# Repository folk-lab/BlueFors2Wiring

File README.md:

# BlueFors2Wiring
Eagle source files for all PCB used in the wiring of BlueFors2

A comprehensive breakdown of how all these parts fit into the fridge can be found on the [Folk Lab wiki](https://qdot-server.phas.ubc.ca/wiki/machines:bluefors_fridge_2:wiring)

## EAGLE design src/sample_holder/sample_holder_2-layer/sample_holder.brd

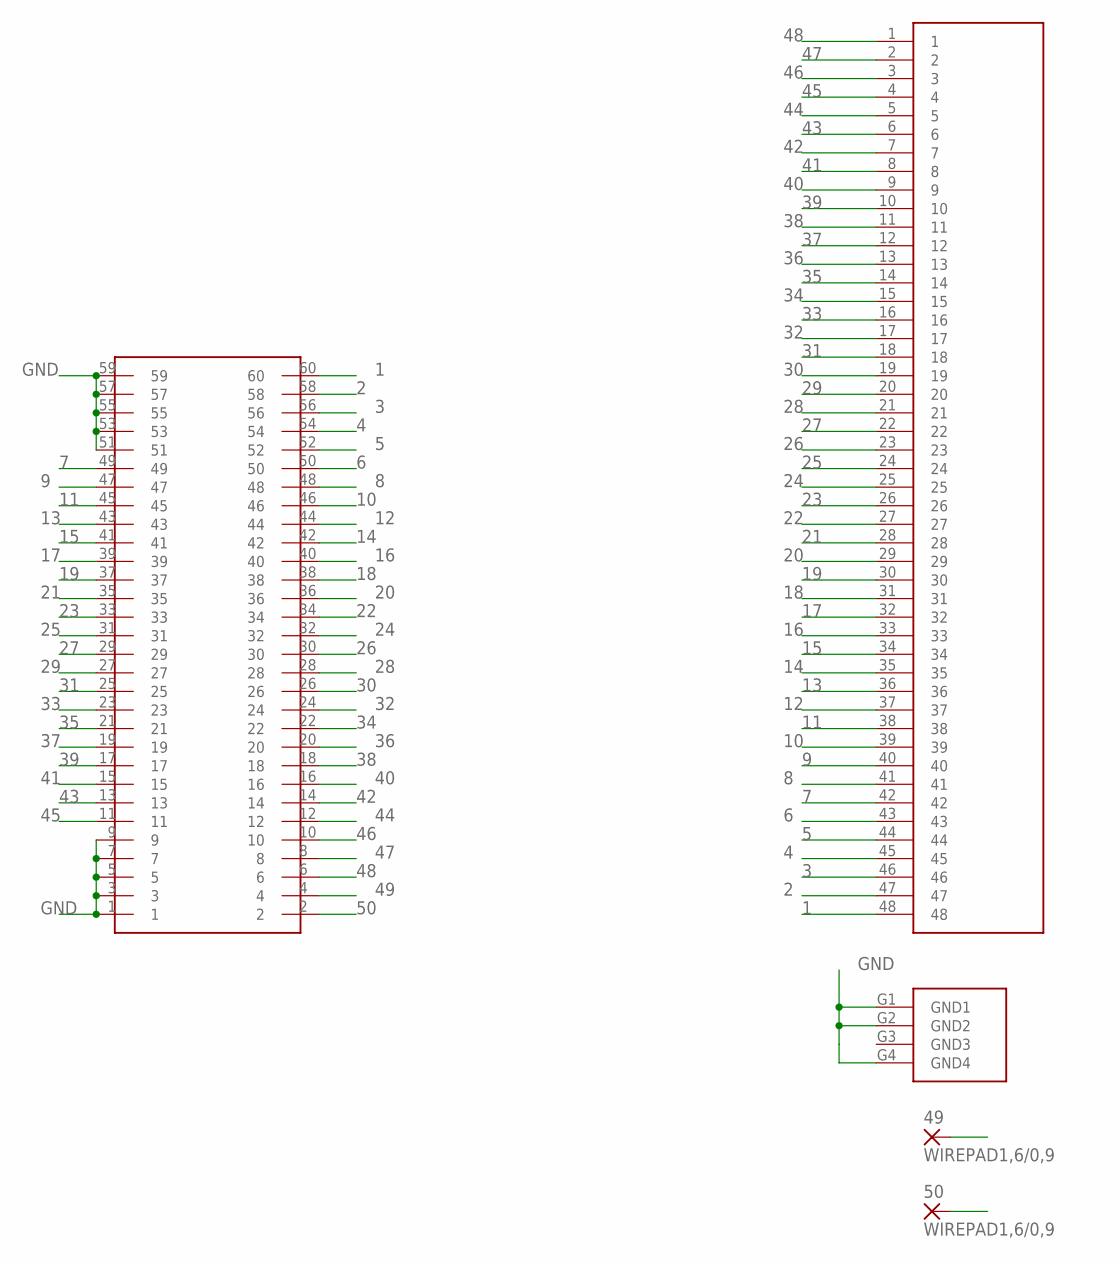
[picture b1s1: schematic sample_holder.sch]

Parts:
49, 50: WIREPAD1,6/0,9; 1,6/0,9
U$1: MEC5-030-CARD-ALL; MEC-030-CARD-ALL
U$2: FOLKLAB-48PADS

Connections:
1: U$1.60, U$2.48
2: U$1.58, U$2.47
3: U$1.56, U$2.46
4: U$1.54, U$2.45
5: U$1.52, U$2.44
6: U$1.50, U$2.43
7: U$1.49, U$2.42
8: U$1.48, U$2.41
9: U$1.47, U$2.40
10: U$1.46, U$2.39
11: U$1.45, U$2.38
12: U$1.44, U$2.37
13: U$1.43, U$2.36
14: U$1.42, U$2.35
15: U$1.41, U$2.34
16: U$1.40, U$2.33
17: U$1.39, U$2.32
18: U$1.38, U$2.31
19: U$1.37, U$2.30
20: U$1.36, U$2.29
21: U$1.35, U$2.28
22: U$1.34, U$2.27
23: U$1.33, U$2.26
24: U$1.32, U$2.25
25: U$1.31, U$2.24
26: U$1.30, U$2.23
27: U$1.29, U$2.22
28: U$1.28, U$2.21
29: U$1.27, U$2.20
30: U$1.26, U$2.19
31: U$1.25, U$2.18
32: U$1.24, U$2.17
33: U$1.23, U$2.16
34: U$1.22, U$2.15
35: U$1.21, U$2.14
36: U$1.20, U$2.13
37: U$1.19, U$2.12
38: U$1.18, U$2.11
39: U$1.17, U$2.10
40: U$1.16, U$2.9
41: U$1.15, U$2.8
42: U$1.14, U$2.7
43: U$1.13, U$2.6
44: U$1.12, U$2.5
45: U$1.11, U$2.4
46: U$1.10, U$2.3
47: U$1.8, U$2.2
48: U$1.6, U$2.1
49: 49.1, U$1.4
50: 50.1, U$1.2
GND: U$1.1, U$1.3, U$1.5, U$1.7, U$1.9, U$1.51, U$1.53, U$1.55, U$1.57, U$1.59, U$2.G1 (GND1), U$2.G2 (GND2), U$2.G4 (GND4)

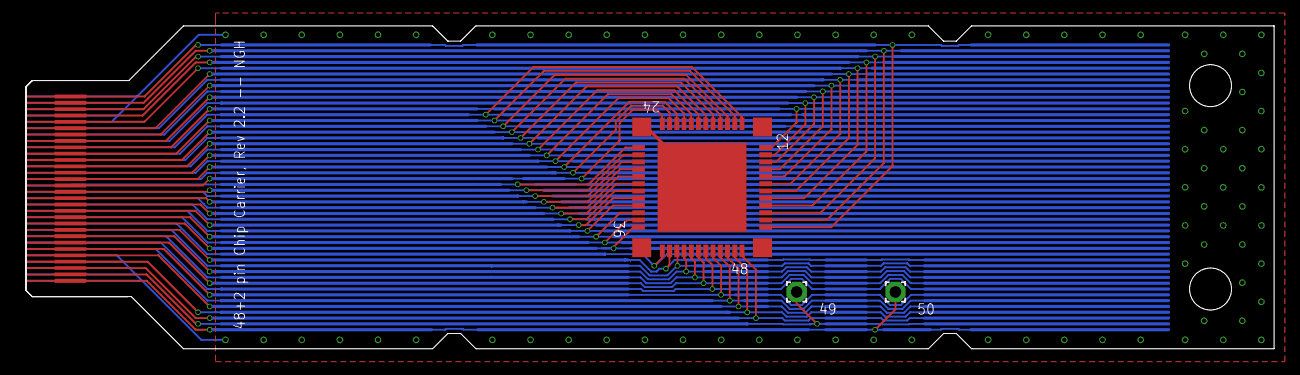
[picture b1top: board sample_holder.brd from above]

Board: 2 copper layers, 98.2 x 25.4 mm, 4 parts (0 on the bottom side), 51 nets.

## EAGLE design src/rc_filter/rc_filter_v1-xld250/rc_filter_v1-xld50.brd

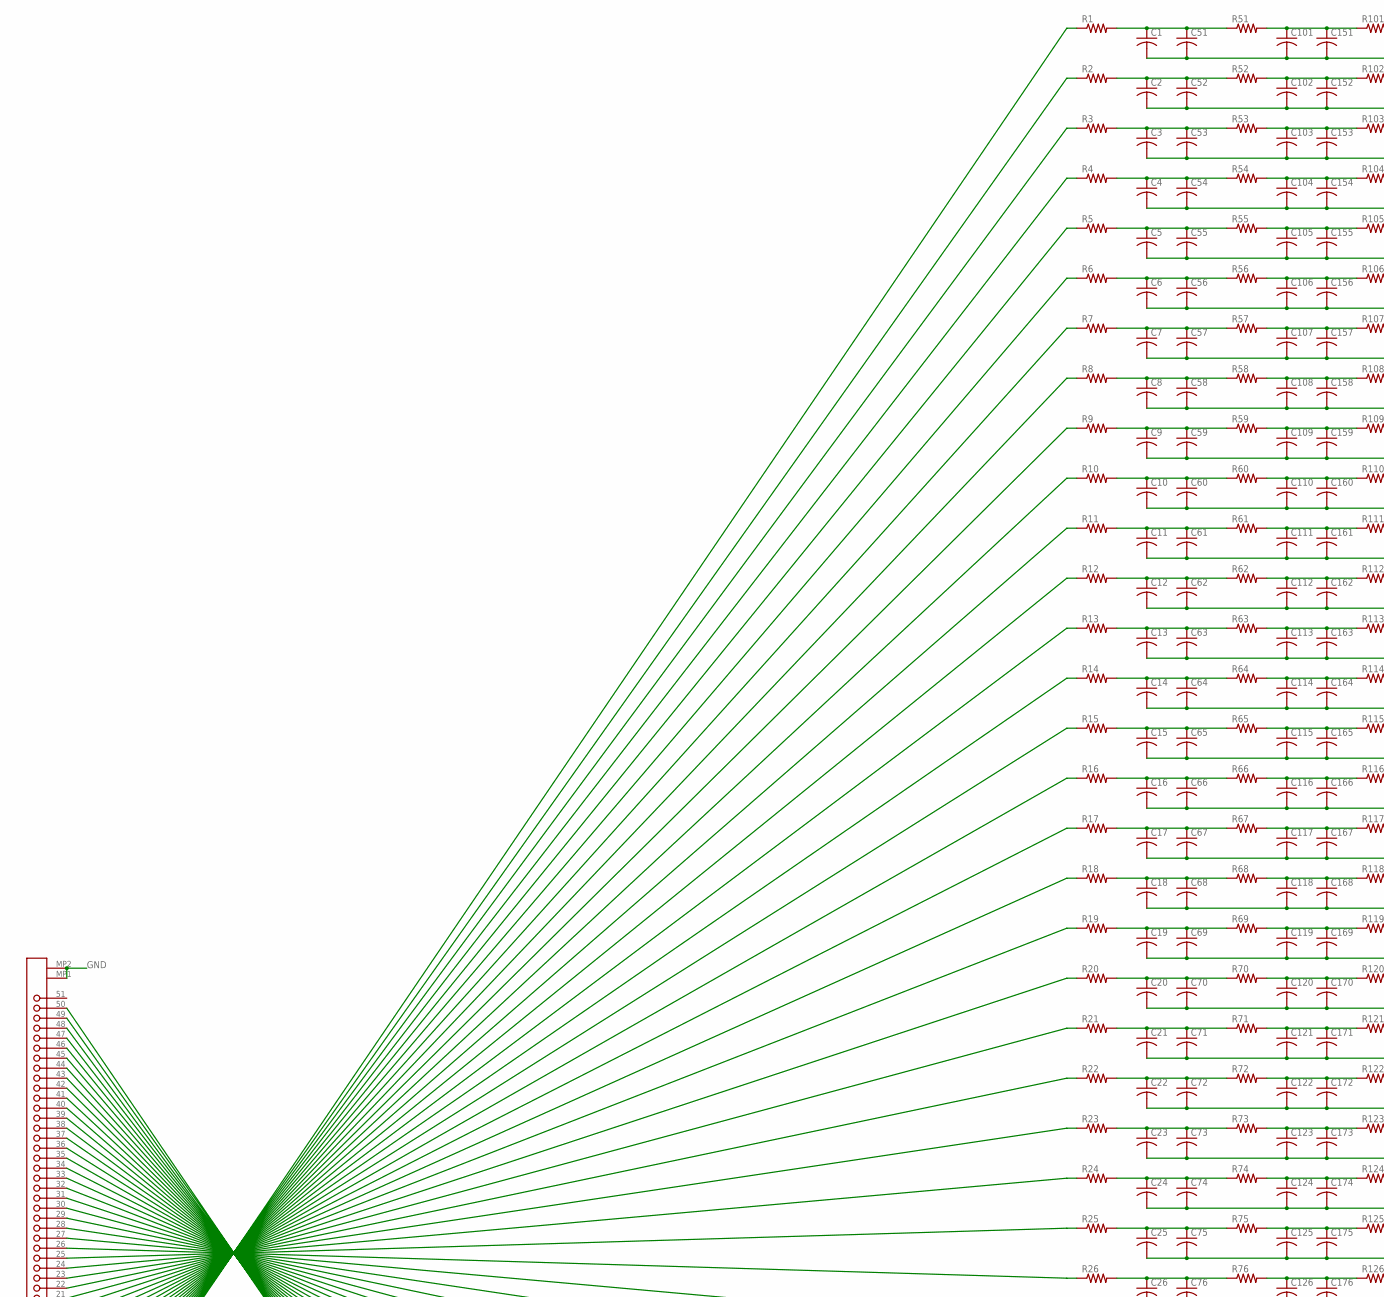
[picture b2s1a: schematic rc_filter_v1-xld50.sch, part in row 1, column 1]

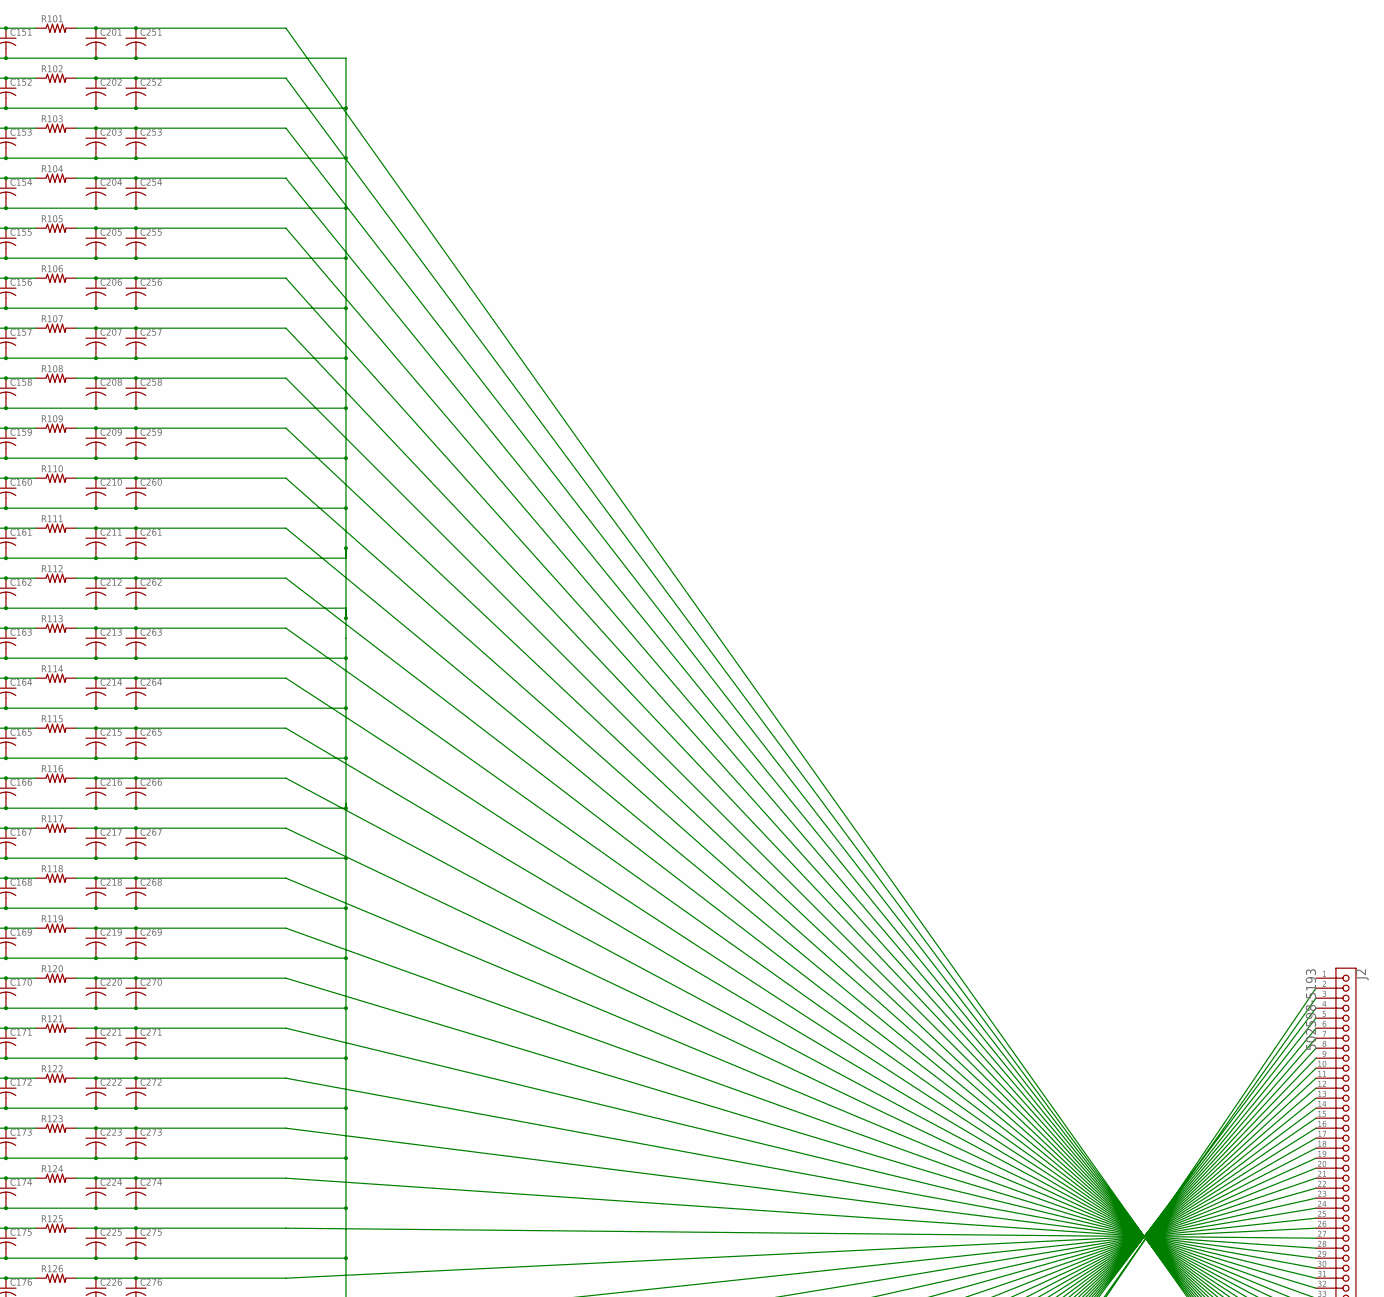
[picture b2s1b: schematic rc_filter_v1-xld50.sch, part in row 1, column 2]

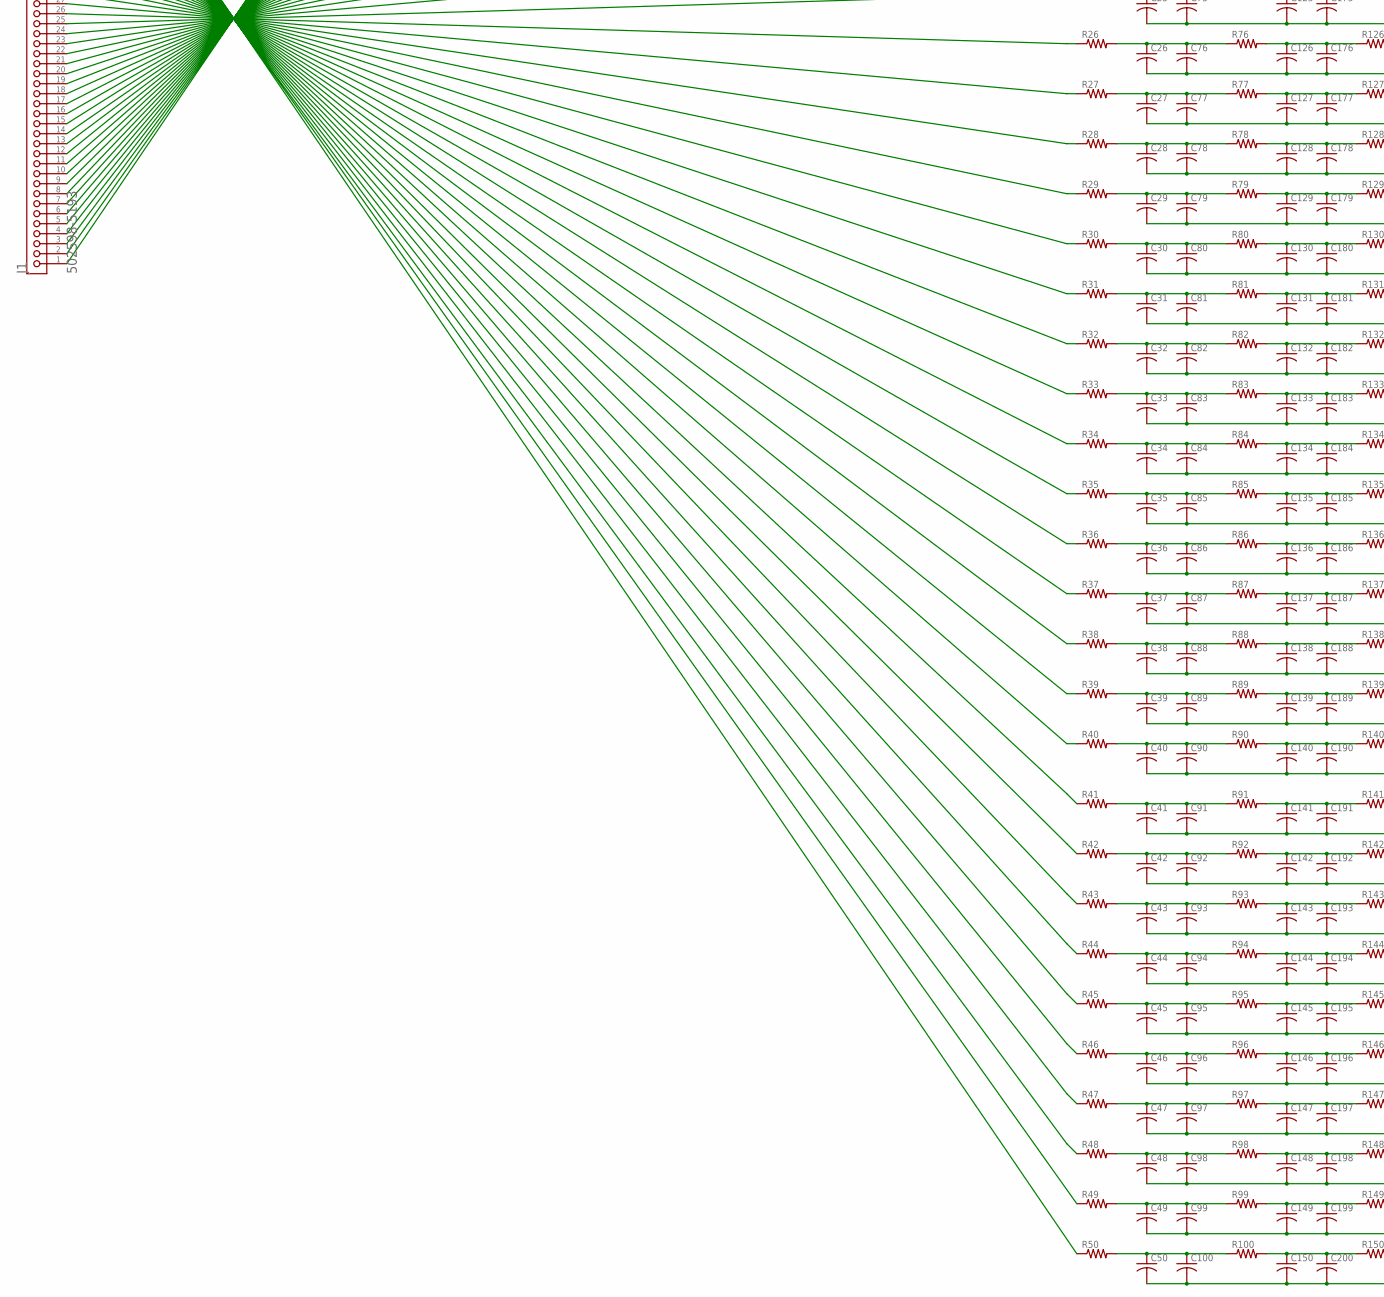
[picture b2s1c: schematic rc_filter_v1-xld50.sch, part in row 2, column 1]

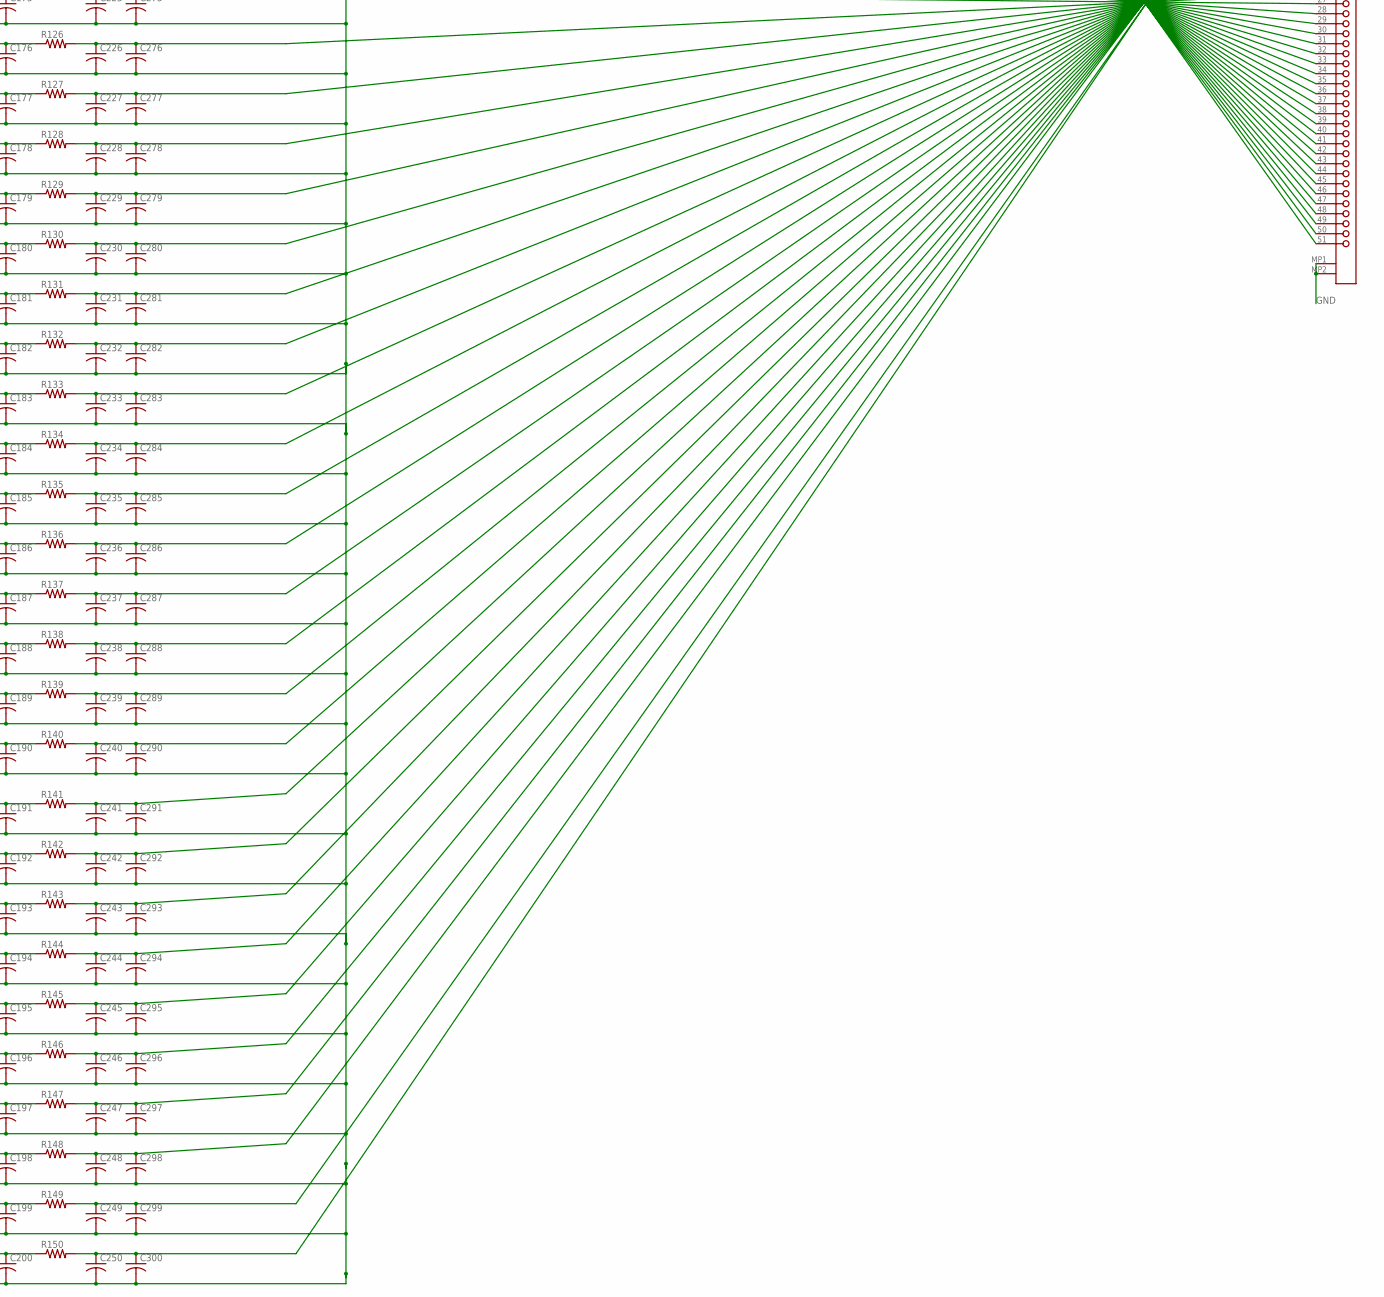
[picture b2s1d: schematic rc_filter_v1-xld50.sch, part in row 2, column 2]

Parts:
C1, C2, C3, C4, C5, C6, C7, C8, C9, C10, C11, C12, C13, C14, C15, C16, C17, C18, C19, C20, C21, C22, C23, C24, C25, C26, C27, C28, C29, C30, C31, C32, C33, C34, C35, C36, C37, C38, C39, C40, C41, C42, C43, C44, C45, C46, C47, C48, C49, C50, C51, C52, C53, C54, C55, C56, C57, C58, C59, C60, C61, C62, C63, C64, C65, C66, C67, C68, C69, C70, C71, C72, C73, C74, C75, C76, C77, C78, C79, C80, C81, C82, C83, C84, C85, C86, C87, C88, C89, C90, C91, C92, C93, C94, C95, C96, C97, C98, C99, C100, C101, C102, C103, C104, C105, C106, C107, C108, C109, C110, C111, C112, C113, C114, C115, C116, C117, C118, C119, C120, C121, C122, C123, C124, C125, C126, C127, C128, C129, C130, C131, C132, C133, C134, C135, C136, C137, C138, C139, C140, C141, C142, C143, C144, C145, C146, C147, C148, C149, C150, C151, C152, C153, C154, C155, C156, C157, C158, C159, C160, C161, C162, C163, C164, C165, C166, C167, C168, C169, C170, C171, C172, C173, C174, C175, C176, C177, C178, C179, C180, C181, C182, C183, C184, C185, C186, C187, C188, C189, C190, C191, C192, C193, C194, C195, C196, C197, C198, C199, C200, C201, C202, C203, C204, C205, C206, C207, C208, C209, C210, C211, C212, C213, C214, C215, C216, C217, C218, C219, C220, C221, C222, C223, C224, C225, C226, C227, C228, C229, C230, C231, C232, C233, C234, C235, C236, C237, C238, C239, C240, C241, C242, C243, C244, C245, C246, C247, C248, C249, C250, C251, C252, C253, C254, C255, C256, C257, C258, C259, C260, C261, C262, C263, C264, C265, C266, C267, C268, C269, C270, C271, C272, C273, C274, C275, C276, C277, C278, C279, C280, C281, C282, C283, C284, C285, C286, C287, C288, C289, C290, C291, C292, C293, C294, C295, C296, C297, C298, C299, C300: C-USC0402; C0402
J1, J2: MOLEX_502598-5193MOLEX_502598-5193_0_0; MOLEX_502598-5193_0
R1, R2, R3, R4, R5, R6, R7, R8, R9, R10, R11, R12, R13, R14, R15, R16, R17, R18, R19, R20, R21, R22, R23, R24, R25, R26, R27, R28, R29, R30, R31, R32, R33, R34, R35, R36, R37, R38, R39, R40, R41, R42, R43, R44, R45, R46, R47, R48, R49, R50, R51, R52, R53, R54, R55, R56, R57, R58, R59, R60, R61, R62, R63, R64, R65, R66, R67, R68, R69, R70, R71, R72, R73, R74, R75, R76, R77, R78, R79, R80, R81, R82, R83, R84, R85, R86, R87, R88, R89, R90, R91, R92, R93, R94, R95, R96, R97, R98, R99, R100, R101, R102, R103, R104, R105, R106, R107, R108, R109, R110, R111, R112, R113, R114, R115, R116, R117, R118, R119, R120, R121, R122, R123, R124, R125, R126, R127, R128, R129, R130, R131, R132, R133, R134, R135, R136, R137, R138, R139, R140, R141, R142, R143, R144, R145, R146, R147, R148, R149, R150: R-US_R0402; R0402

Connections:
F1: J1.1, R1.1
F2: J1.2, R2.1
F3: J1.3, R3.1
F4: J1.4, R4.1
F5: J1.5, R5.1
F6: J1.6, R6.1
F7: J1.7, R7.1
F8: J1.8, R8.1
F9: J1.9, R9.1
F10: J1.10, R10.1
F11: J1.11, R11.1
F12: J1.12, R12.1
F13: J1.13, R13.1
F14: J1.14, R14.1
F15: J1.15, R15.1
F16: J1.16, R16.1
F17: J1.17, R17.1
F18: J1.18, R18.1
F19: J1.19, R19.1
F20: J1.20, R20.1
F21: J1.21, R21.1
F22: J1.22, R22.1
F23: J1.23, R23.1
F24: J1.24, R24.1
F25: J1.25, R25.1
F26: J1.26, R26.1
F27: J1.27, R27.1
F28: J1.28, R28.1
F29: J1.29, R29.1
F30: J1.30, R30.1
F31: J1.31, R31.1
F32: J1.32, R32.1
F33: J1.33, R33.1
F34: J1.34, R34.1
F35: J1.35, R35.1
F36: J1.36, R36.1
F37: J1.37, R37.1
F38: J1.38, R38.1
F39: J1.39, R39.1
F40: J1.40, R40.1
F41: J1.41, R41.1
F42: J1.42, R42.1
F43: J1.43, R43.1
F44: J1.44, R44.1
F45: J1.45, R45.1
F46: J1.46, R46.1
F47: J1.47, R47.1
F48: J1.48, R48.1
F49: J1.49, R49.1
F50: J1.50, R50.1
G1: C201.1, C251.1, J2.51, R101.2
G2: C202.1, C252.1, J2.50, R102.2
G3: C203.1, C253.1, J2.49, R103.2
G4: C204.1, C254.1, J2.48, R104.2
G5: C205.1, C255.1, J2.47, R105.2
G6: C206.1, C256.1, J2.46, R106.2
G7: C207.1, C257.1, J2.45, R107.2
G8: C208.1, C258.1, J2.44, R108.2
G9: C209.1, C259.1, J2.43, R109.2
G10: C210.1, C260.1, J2.42, R110.2
G11: C211.1, C261.1, J2.41, R111.2
G12: C212.1, C262.1, J2.40, R112.2
G13: C213.1, C263.1, J2.39, R113.2
G14: C214.1, C264.1, J2.38, R114.2
G15: C215.1, C265.1, J2.37, R115.2
G16: C216.1, C266.1, J2.36, R116.2
G17: C217.1, C267.1, J2.35, R117.2
G18: C218.1, C268.1, J2.34, R118.2
G19: C219.1, C269.1, J2.33, R119.2
G20: C220.1, C270.1, J2.32, R120.2
G21: C221.1, C271.1, J2.31, R121.2
G22: C222.1, C272.1, J2.30, R122.2
G23: C223.1, C273.1, J2.29, R123.2
G24: C224.1, C274.1, J2.28, R124.2
G25: C225.1, C275.1, J2.27, R125.2
G26: C226.1, C276.1, J2.26, R126.2
G27: C227.1, C277.1, J2.25, R127.2
G28: C228.1, C278.1, J2.24, R128.2
G29: C229.1, C279.1, J2.23, R129.2
G30: C230.1, C280.1, J2.22, R130.2
G31: C231.1, C281.1, J2.21, R131.2
G32: C232.1, C282.1, J2.20, R132.2
G33: C233.1, C283.1, J2.19, R133.2
G34: C234.1, C284.1, J2.18, R134.2
G35: C235.1, C285.1, J2.17, R135.2
G36: C236.1, C286.1, J2.16, R136.2
G37: C237.1, C287.1, J2.15, R137.2
G38: C238.1, C288.1, J2.14, R138.2
G39: C239.1, C289.1, J2.13, R139.2
G40: C240.1, C290.1, J2.12, R140.2
G41: C241.1, C291.1, J2.11, R141.2
G42: C242.1, C292.1, J2.10, R142.2
G43: C243.1, C293.1, J2.9, R143.2
G44: C244.1, C294.1, J2.8, R144.2
G45: C245.1, C295.1, J2.7, R145.2
G46: C246.1, C296.1, J2.6, R146.2
G47: C247.1, C297.1, J2.5, R147.2
G48: C248.1, C298.1, J2.4, R148.2
G49: C249.1, C299.1, J2.3, R149.2
G50: C250.1, C300.1, J2.2, R150.2
GND: C1.2, C2.2, C3.2, C4.2, C5.2, C6.2, C7.2, C8.2, C9.2, C10.2, C11.2, C12.2, C13.2, C14.2, C15.2, C16.2, C17.2, C18.2, C19.2, C20.2, C21.2, C22.2, C23.2, C24.2, C25.2, C26.2, C27.2, C28.2, C29.2, C30.2, C31.2, C32.2, C33.2, C34.2, C35.2, C36.2, C37.2, C38.2, C39.2, C40.2, C41.2, C42.2, C43.2, C44.2, C45.2, C46.2, C47.2, C48.2, C49.2, C50.2, C51.2, C52.2, C53.2, C54.2, C55.2, C56.2, C57.2, C58.2, C59.2, C60.2, C61.2, C62.2, C63.2, C64.2, C65.2, C66.2, C67.2, C68.2, C69.2, C70.2, C71.2, C72.2, C73.2, C74.2, C75.2, C76.2, C77.2, C78.2, C79.2, C80.2, C81.2, C82.2, C83.2, C84.2, C85.2, C86.2, C87.2, C88.2, C89.2, C90.2, C91.2, C92.2, C93.2, C94.2, C95.2, C96.2, C97.2, C98.2, C99.2, C100.2, C101.2, C102.2, C103.2, C104.2, C105.2, C106.2, C107.2, C108.2, C109.2, C110.2, C111.2, C112.2, C113.2, C114.2, C115.2, C116.2, C117.2, C118.2, C119.2, C120.2, C121.2, C122.2, C123.2, C124.2, C125.2, C126.2, C127.2, C128.2, C129.2, C130.2, C131.2, C132.2, C133.2, C134.2, C135.2, C136.2, C137.2, C138.2, C139.2, C140.2, C141.2, C142.2, C143.2, C144.2, C145.2, C146.2, C147.2, C148.2, C149.2, C150.2, C151.2, C152.2, C153.2, C154.2, C155.2, C156.2, C157.2, C158.2, C159.2, C160.2, C161.2, C162.2, C163.2, C164.2, C165.2, C166.2, C167.2, C168.2, C169.2, C170.2, C171.2, C172.2, C173.2, C174.2, C175.2, C176.2, C177.2, C178.2, C179.2, C180.2, C181.2, C182.2, C183.2, C184.2, C185.2, C186.2, C187.2, C188.2, C189.2, C190.2, C191.2, C192.2, C193.2, C194.2, C195.2, C196.2, C197.2, C198.2, C199.2, C200.2, C201.2, C202.2, C203.2, C204.2, C205.2, C206.2, C207.2, C208.2, C209.2, C210.2, C211.2, C212.2, C213.2, C214.2, C215.2, C216.2, C217.2, C218.2, C219.2, C220.2, C221.2, C222.2, C223.2, C224.2, C225.2, C226.2, C227.2, C228.2, C229.2, C230.2, C231.2, C232.2, C233.2, C234.2, C235.2, C236.2, C237.2, C238.2, C239.2, C240.2, C241.2, C242.2, C243.2, C244.2, C245.2, C246.2, C247.2, C248.2, C249.2, C250.2, C251.2, C252.2, C253.2, C254.2, C255.2, C256.2, C257.2, C258.2, C259.2, C260.2, C261.2, C262.2, C263.2, C264.2, C265.2, C266.2, C267.2, C268.2, C269.2, C270.2, C271.2, C272.2, C273.2, C274.2, C275.2, C276.2, C277.2, C278.2, C279.2, C280.2, C281.2, C282.2, C283.2, C284.2, C285.2, C286.2, C287.2, C288.2, C289.2, C290.2, C291.2, C292.2, C293.2, C294.2, C295.2, C296.2, C297.2, C298.2, C299.2, C300.2, J1.MP1, J1.MP2, J2.MP1, J2.MP2
unnamed: C4.1, C54.1, R4.2, R54.1
unnamed: C104.1, C154.1, R54.2, R104.1
unnamed: C3.1, C53.1, R3.2, R53.1
unnamed: C103.1, C153.1, R53.2, R103.1
unnamed: C6.1, C56.1, R6.2, R56.1
unnamed: C106.1, C156.1, R56.2, R106.1
unnamed: C5.1, C55.1, R5.2, R55.1
unnamed: C105.1, C155.1, R55.2, R105.1
unnamed: C8.1, C58.1, R8.2, R58.1
unnamed: C108.1, C158.1, R58.2, R108.1
unnamed: C7.1, C57.1, R7.2, R57.1
unnamed: C107.1, C157.1, R57.2, R107.1
unnamed: C10.1, C60.1, R10.2, R60.1
unnamed: C110.1, C160.1, R60.2, R110.1
unnamed: C9.1, C59.1, R9.2, R59.1
unnamed: C109.1, C159.1, R59.2, R109.1
unnamed: C2.1, C52.1, R2.2, R52.1
unnamed: C102.1, C152.1, R52.2, R102.1
unnamed: C1.1, C51.1, R1.2, R51.1
unnamed: C101.1, C151.1, R51.2, R101.1
unnamed: C12.1, C62.1, R12.2, R62.1
unnamed: C112.1, C162.1, R62.2, R112.1
unnamed: C11.1, C61.1, R11.2, R61.1
unnamed: C111.1, C161.1, R61.2, R111.1
unnamed: C14.1, C64.1, R14.2, R64.1
unnamed: C114.1, C164.1, R64.2, R114.1
unnamed: C13.1, C63.1, R13.2, R63.1
unnamed: C113.1, C163.1, R63.2, R113.1
unnamed: C16.1, C66.1, R16.2, R66.1
unnamed: C116.1, C166.1, R66.2, R116.1
unnamed: C15.1, C65.1, R15.2, R65.1
unnamed: C115.1, C165.1, R65.2, R115.1
unnamed: C18.1, C68.1, R18.2, R68.1
unnamed: C118.1, C168.1, R68.2, R118.1
unnamed: C17.1, C67.1, R17.2, R67.1
unnamed: C117.1, C167.1, R67.2, R117.1
unnamed: C20.1, C70.1, R20.2, R70.1
unnamed: C120.1, C170.1, R70.2, R120.1
unnamed: C19.1, C69.1, R19.2, R69.1
unnamed: C119.1, C169.1, R69.2, R119.1
unnamed: C42.1, C92.1, R42.2, R92.1
unnamed: C142.1, C192.1, R92.2, R142.1
unnamed: C41.1, C91.1, R41.2, R91.1
unnamed: C141.1, C191.1, R91.2, R141.1
unnamed: C44.1, C94.1, R44.2, R94.1
unnamed: C144.1, C194.1, R94.2, R144.1
unnamed: C43.1, C93.1, R43.2, R93.1
unnamed: C143.1, C193.1, R93.2, R143.1
unnamed: C46.1, C96.1, R46.2, R96.1
unnamed: C146.1, C196.1, R96.2, R146.1
unnamed: C45.1, C95.1, R45.2, R95.1
unnamed: C145.1, C195.1, R95.2, R145.1
unnamed: C48.1, C98.1, R48.2, R98.1
unnamed: C148.1, C198.1, R98.2, R148.1
unnamed: C47.1, C97.1, R47.2, R97.1
unnamed: C147.1, C197.1, R97.2, R147.1
unnamed: C50.1, C100.1, R50.2, R100.1
unnamed: C150.1, C200.1, R100.2, R150.1
unnamed: C49.1, C99.1, R49.2, R99.1
unnamed: C149.1, C199.1, R99.2, R149.1
unnamed: C32.1, C82.1, R32.2, R82.1
unnamed: C132.1, C182.1, R82.2, R132.1
unnamed: C31.1, C81.1, R31.2, R81.1
unnamed: C131.1, C181.1, R81.2, R131.1
unnamed: C34.1, C84.1, R34.2, R84.1
unnamed: C134.1, C184.1, R84.2, R134.1
unnamed: C33.1, C83.1, R33.2, R83.1
unnamed: C133.1, C183.1, R83.2, R133.1
unnamed: C36.1, C86.1, R36.2, R86.1
unnamed: C136.1, C186.1, R86.2, R136.1
unnamed: C35.1, C85.1, R35.2, R85.1
unnamed: C135.1, C185.1, R85.2, R135.1
unnamed: C38.1, C88.1, R38.2, R88.1
unnamed: C138.1, C188.1, R88.2, R138.1
unnamed: C37.1, C87.1, R37.2, R87.1
unnamed: C137.1, C187.1, R87.2, R137.1
unnamed: C40.1, C90.1, R40.2, R90.1
unnamed: C140.1, C190.1, R90.2, R140.1
unnamed: C39.1, C89.1, R39.2, R89.1
unnamed: C139.1, C189.1, R89.2, R139.1
unnamed: C22.1, C72.1, R22.2, R72.1
unnamed: C122.1, C172.1, R72.2, R122.1
unnamed: C21.1, C71.1, R21.2, R71.1
unnamed: C121.1, C171.1, R71.2, R121.1
unnamed: C24.1, C74.1, R24.2, R74.1
unnamed: C124.1, C174.1, R74.2, R124.1
unnamed: C23.1, C73.1, R23.2, R73.1
unnamed: C123.1, C173.1, R73.2, R123.1
unnamed: C26.1, C76.1, R26.2, R76.1
unnamed: C126.1, C176.1, R76.2, R126.1
unnamed: C25.1, C75.1, R25.2, R75.1
unnamed: C125.1, C175.1, R75.2, R125.1
unnamed: C28.1, C78.1, R28.2, R78.1
unnamed: C128.1, C178.1, R78.2, R128.1
unnamed: C27.1, C77.1, R27.2, R77.1
unnamed: C127.1, C177.1, R77.2, R127.1
unnamed: C30.1, C80.1, R30.2, R80.1
unnamed: C130.1, C180.1, R80.2, R130.1
unnamed: C29.1, C79.1, R29.2, R79.1
unnamed: C129.1, C179.1, R79.2, R129.1

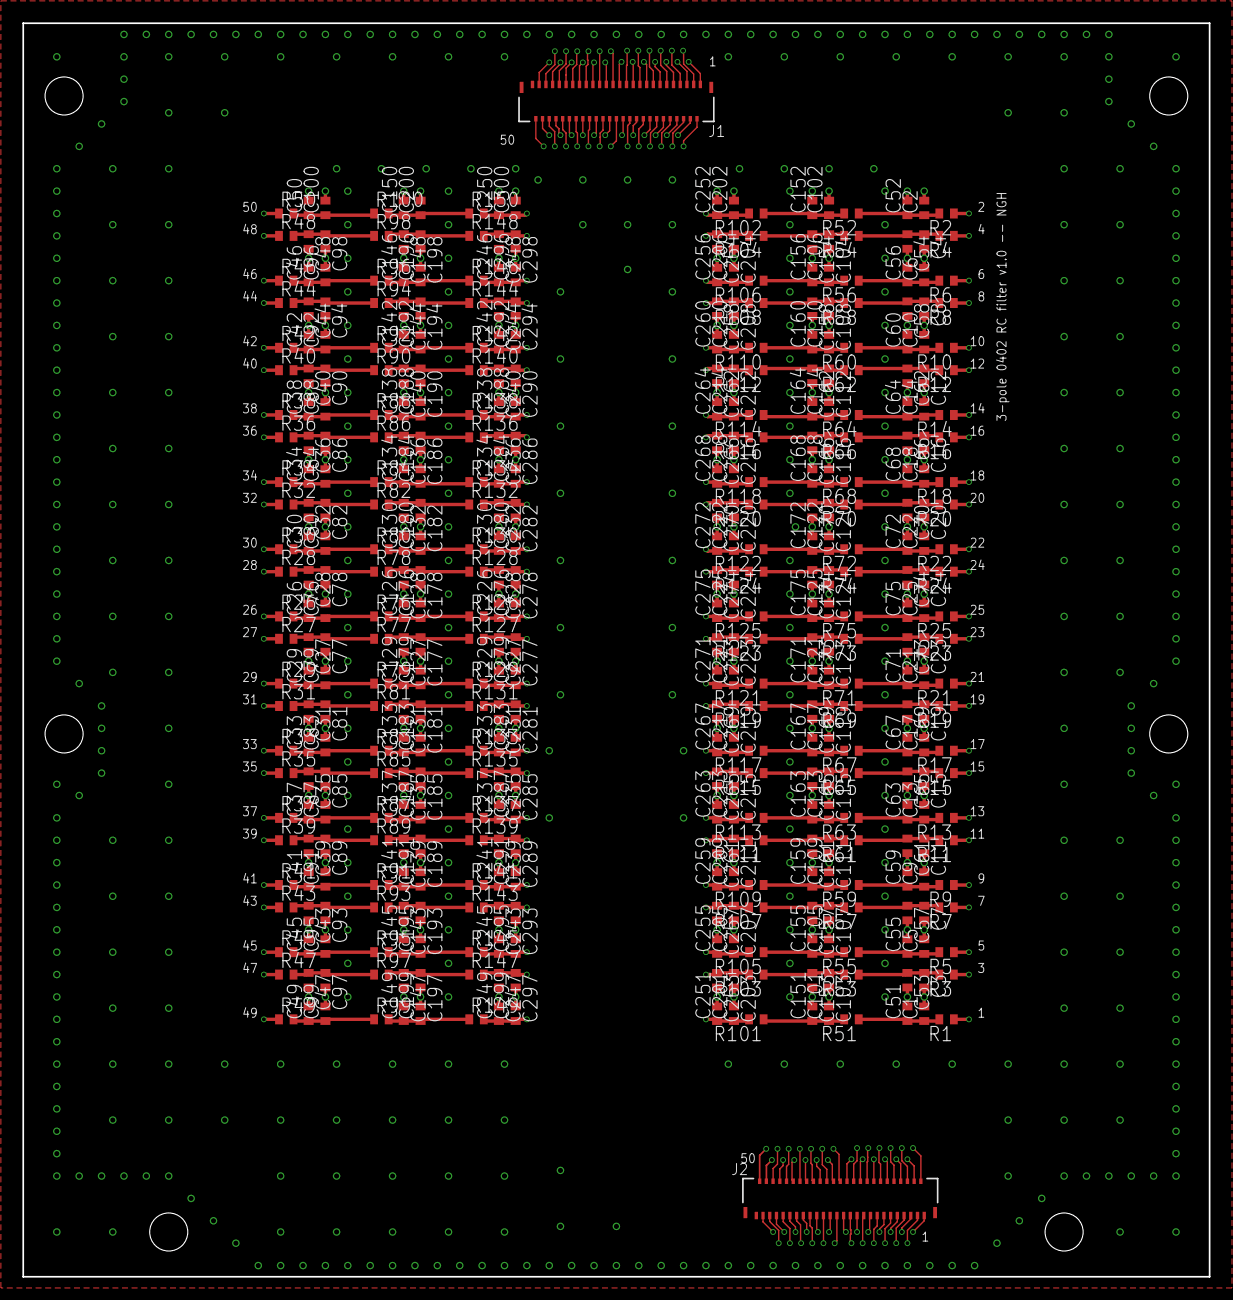
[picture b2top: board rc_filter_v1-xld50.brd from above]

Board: 4 copper layers, 106.0 x 112.0 mm, 452 parts (0 on the bottom side), 201 nets.

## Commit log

2019-09-13 Add files via upload
    first set of eagle files added
2019-09-13 naming change
2019-09-13 more files
2019-09-13 added files
